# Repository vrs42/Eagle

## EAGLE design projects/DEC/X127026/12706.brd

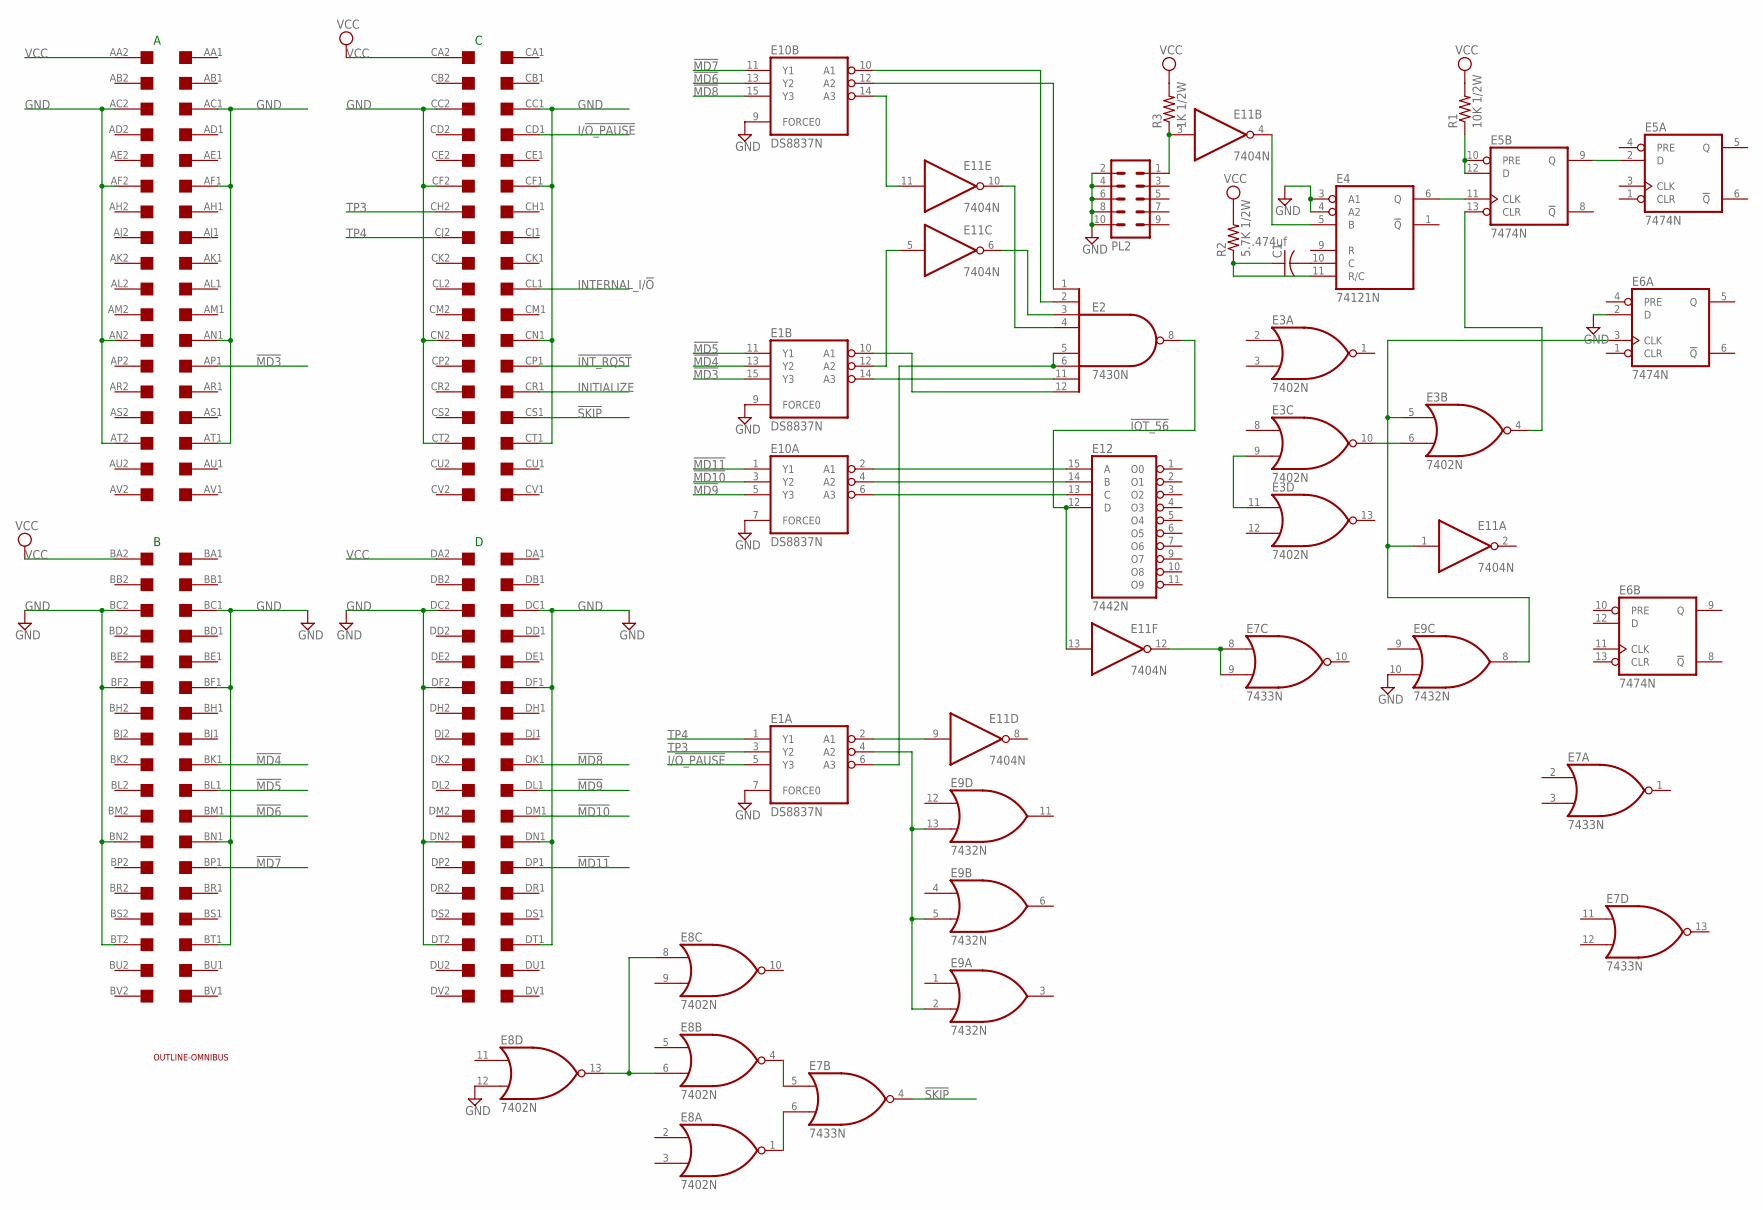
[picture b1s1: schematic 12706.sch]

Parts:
C1: .474uf; C050-045X075
E1, E10: DS8837N; DIL16
E2: 7430N; DIL14
E3, E8: 7402N; DIL14
E4: 74121N; DIL14
E5, E6: 7474N; DIL14
E7: 7433N; DIL14
E9: 7432N; DIL14
E11: 7404N; DIL14
E12: 7442N; DIL16
PL2: 10H
R1: 10K 1/2W; 0204/7
R2: 5.7K 1/2W; 0204/7
R3: 1K 1/2W; 0204/7
U$1: QUAD; EDGE-CON8
U$2: OUTLINE-OMNIBUS; OMNIBUS

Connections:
!INT_RQST: U$1.CP1
!IOT_56: E2.8 (O), E11.13 (I), E12.12 (D)
!MD3: E1.15 (Y3), U$1.AP1
!MD4: E1.13 (Y2), U$1.BK1
!MD5: E1.11 (Y1), U$1.BL1
!MD6: E10.13 (Y2), U$1.BM1
!MD7: E10.11 (Y1), U$1.BP1
!MD8: E10.15 (Y3), U$1.DK1
!MD9: E10.5 (Y3), U$1.DL1
!MD10: E10.3 (Y2), U$1.DM1
!MD11: E10.1 (Y1), U$1.DP1
!SKIP: E7.4 (O), U$1.CS1
GND: E1.7 (FORCE0), E1.8 (GND), E1.9 (FORCE0), E2.7 (GND), E3.7 (GND), E4.3 (A1), E4.4 (A2), E4.7 (GND), E5.7 (GND), E6.2 (D), E6.7 (GND), E7.7 (GND), E8.7 (GND), E8.12 (I1), E9.7 (GND), E9.10 (I1), E10.7 (FORCE0), E10.8 (GND), E10.9 (FORCE0), E11.7 (GND), E12.8 (GND), PL2.2, PL2.4, PL2.6, PL2.8, PL2.10, U$1.AC1, U$1.AC2, U$1.AF1, U$1.AF2, U$1.AN1, U$1.AN2, U$1.AT1, U$1.AT2, U$1.BC1, U$1.BC2, U$1.BF1, U$1.BF2, U$1.BN1, U$1.BN2, U$1.BT1, U$1.BT2, U$1.CC1, U$1.CC2, U$1.CF1, U$1.CF2, U$1.CN1, U$1.CN2, U$1.CT1, U$1.CT2, U$1.DC1, U$1.DC2, U$1.DF1, U$1.DF2, U$1.DN1, U$1.DN2, U$1.DT1, U$1.DT2
I/!O_PAUSE: E1.5 (Y3), U$1.CD1
INITIALIZE: U$1.CR1
INTERNAL_I/!O: U$1.CL1
unnamed: E1.14 (A3), E2.11 (I6)
unnamed: E1.10 (A1), E2.12 (I7)
unnamed: E10.2 (A1), E12.15 (A)
unnamed: E10.4 (A2), E12.14 (B)
unnamed: E10.6 (A3), E12.13 (C)
unnamed: E7.6 (I1), E8.1 (O)
unnamed: E7.8 (I0), E7.9 (I1), E11.12 (O)
unnamed: E1.2 (A1), E11.9 (I)
unnamed: E1.4 (A2), E9.2 (I1), E9.5 (I1), E9.13 (I1)
unnamed: E1.6 (A3), E2.5 (I4), E2.6 (I5)
unnamed: E2.4 (I3), E11.10 (O)
unnamed: E2.1 (I0), E10.12 (A2)
unnamed: E2.2 (I1), E10.10 (A1)
unnamed: E2.3 (I2), E11.6 (O)
unnamed: E1.12 (A2), E11.5 (I)
unnamed: E10.14 (A3), E11.11 (I)
unnamed: E7.5 (I0), E8.4 (O)
unnamed: E8.6 (I1), E8.8 (I0), E8.13 (O)
unnamed: C1.1, E4.11 (R/C), R2.1
unnamed: E5.2 (D), E5.9 (Q)
unnamed: E5.10 (PRE), E5.12 (D), R1.1
unnamed: E3.6 (I1), E3.10 (O)
unnamed: E3.9 (I1), E3.11 (I0)
unnamed: C1.2, E4.10 (C)
unnamed: E4.6 (Q), E5.11 (CLK)
unnamed: E4.5 (B), E11.4 (O)
unnamed: E11.3 (I), PL2.1, R3.1
unnamed: E3.4 (O), E5.13 (CLR)
unnamed: E3.5 (I0), E6.3 (CLK), E9.8 (O), E11.1 (I)
TP3: E1.3 (Y2), U$1.CH2
TP4: E1.1 (Y1), U$1.CJ2
VCC: E1.16 (VCC), E2.14 (VCC), E3.14 (VCC), E4.14 (VCC), E5.14 (VCC), E6.14 (VCC), E7.14 (VCC), E8.14 (VCC), E9.14 (VCC), E10.16 (VCC), E11.14 (VCC), E12.16 (VCC), R1.2, R2.2, R3.2, U$1.AA2, U$1.BA2, U$1.CA2, U$1.DA2

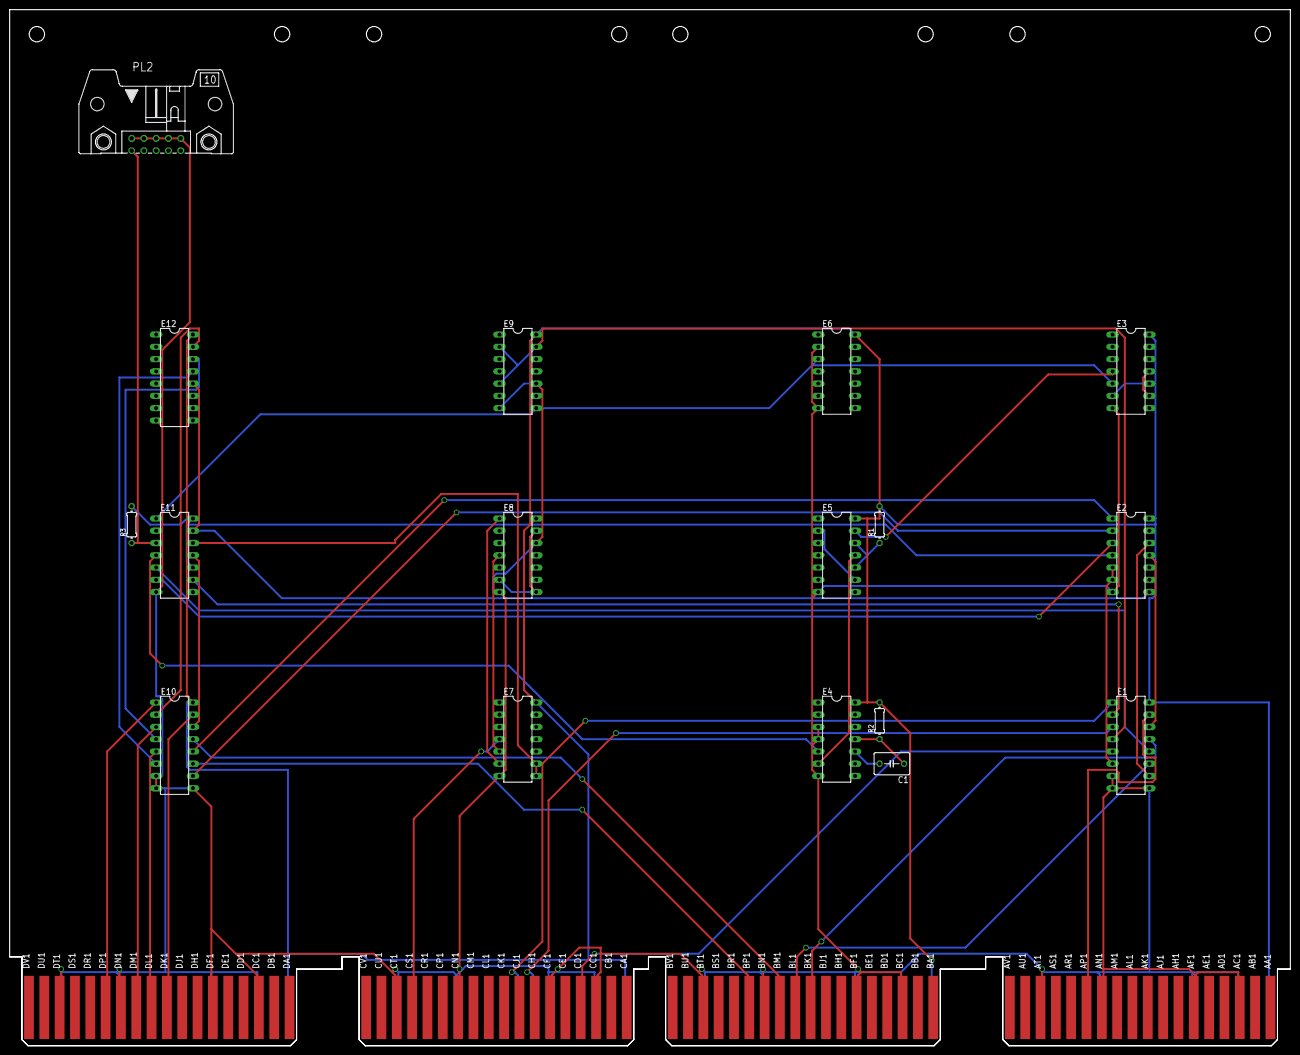
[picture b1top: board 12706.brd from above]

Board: 2 copper layers, 265.3 x 214.6 mm, 19 parts (0 on the bottom side), 45 nets.

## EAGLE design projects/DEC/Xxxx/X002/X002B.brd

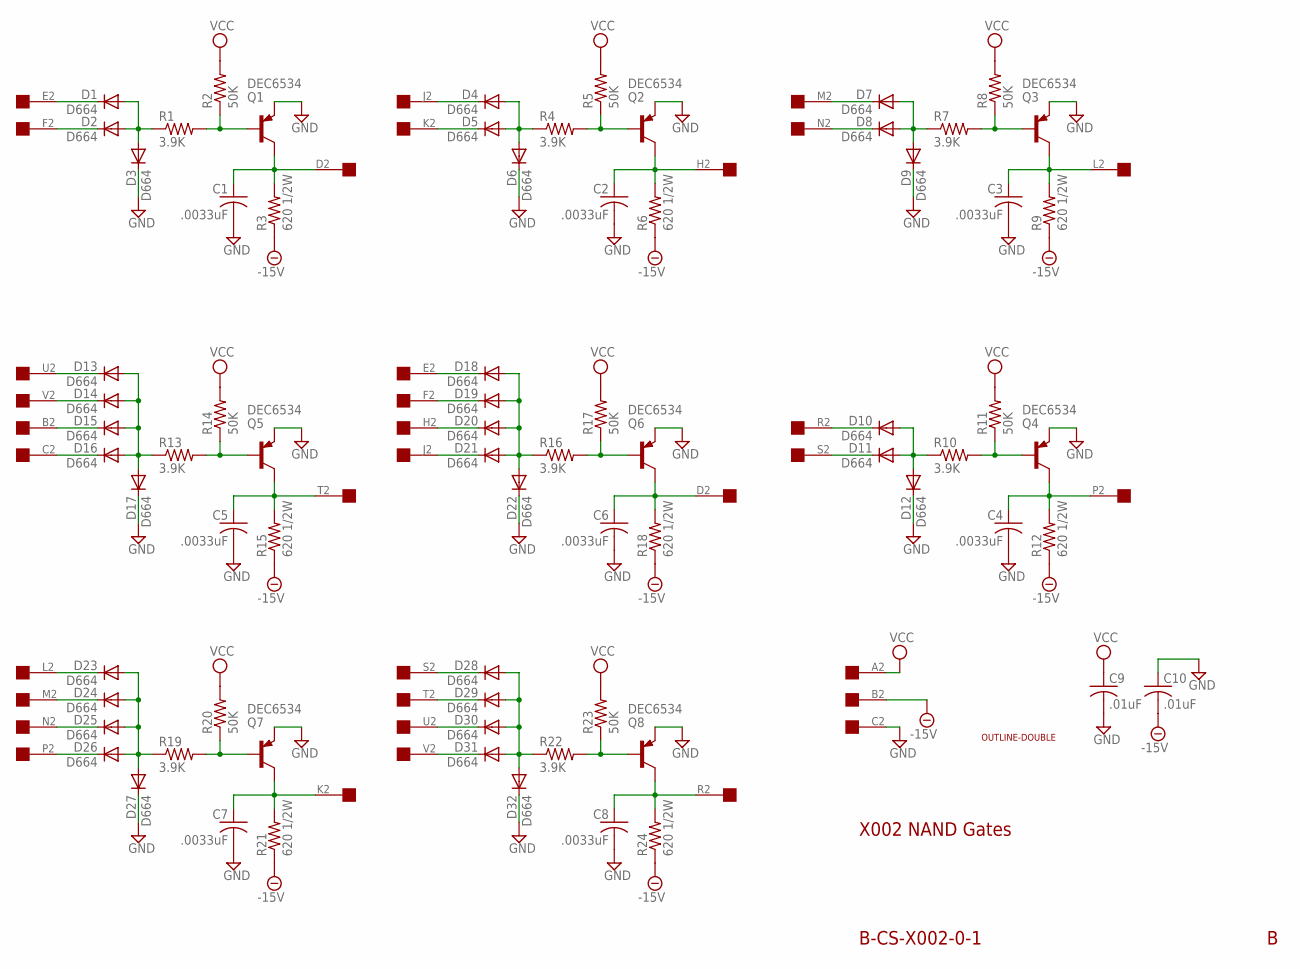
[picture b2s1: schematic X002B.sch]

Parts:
A: EDGE-1; EDGE-CON1
B: EDGE-1; EDGE-CON1
C1, C2, C3, C4, C5, C6, C7, C8: .0033uF; C225-062X268
C9, C10: .01uF; C050-025X075
D1, D2, D3, D4, D5, D6, D7, D8, D9, D10, D11, D12, D13, D14, D15, D16, D17, D18, D19, D20, D21, D22, D23, D24, D25, D26, D27, D28, D29, D30, D31, D32: D664; DO35-10
Q1, Q2, Q3, Q4, Q5, Q6, Q7, Q8: DEC6534; TO5
R1, R4, R7, R10, R13, R16, R19, R22: 3.9K; 0207/10
R2, R5, R8, R11, R14, R17, R20, R23: 50K; 0207/10
R3, R6, R9, R12, R15, R18, R21, R24: 620 1/2W; 0414/15
U$1: OUTLINE-DOUBLE; DOUBLE

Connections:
-15V: A.B2, C10.2, R3.1, R6.1, R9.1, R12.1, R15.1, R18.1, R21.1, R24.1
GND: A.C2, C1.2, C2.2, C3.2, C4.2, C5.2, C6.2, C7.2, C8.2, C9.2, C10.1, D3.C, D6.C, D9.C, D12.C, D17.C, D22.C, D27.C, D32.C, Q1.1 (E), Q2.1 (E), Q3.1 (E), Q4.1 (E), Q5.1 (E), Q6.1 (E), Q7.1 (E), Q8.1 (E)
unnamed: A.F2, D2.C
unnamed: A.E2, D1.C
unnamed: D1.A, D2.A, D3.A, R1.1
unnamed: Q1.2 (B), R1.2, R2.1
unnamed: A.D2, C1.1, Q1.3 (C), R3.2
unnamed: A.K2, D5.C
unnamed: A.J2, D4.C
unnamed: D4.A, D5.A, D6.A, R4.1
unnamed: Q2.2 (B), R4.2, R5.1
unnamed: A.H2, C2.1, Q2.3 (C), R6.2
unnamed: A.N2, D8.C
unnamed: A.M2, D7.C
unnamed: D7.A, D8.A, D9.A, R7.1
unnamed: Q3.2 (B), R7.2, R8.1
unnamed: A.L2, C3.1, Q3.3 (C), R9.2
unnamed: A.S2, D11.C
unnamed: A.R2, D10.C
unnamed: D10.A, D11.A, D12.A, R10.1
unnamed: Q4.2 (B), R10.2, R11.1
unnamed: A.P2, C4.1, Q4.3 (C), R12.2
unnamed: A.V2, D14.C
unnamed: A.U2, D13.C
unnamed: D13.A, D14.A, D15.A, D16.A, D17.A, R13.1
unnamed: Q5.2 (B), R13.2, R14.1
unnamed: A.T2, C5.1, Q5.3 (C), R15.2
unnamed: B.C2, D16.C
unnamed: B.B2, D15.C
unnamed: B.F2, D19.C
unnamed: B.E2, D18.C
unnamed: D18.A, D19.A, D20.A, D21.A, D22.A, R16.1
unnamed: Q6.2 (B), R16.2, R17.1
unnamed: B.D2, C6.1, Q6.3 (C), R18.2
unnamed: B.J2, D21.C
unnamed: B.H2, D20.C
unnamed: B.M2, D24.C
unnamed: B.L2, D23.C
unnamed: D23.A, D24.A, D25.A, D26.A, D27.A, R19.1
unnamed: Q7.2 (B), R19.2, R20.1
unnamed: B.K2, C7.1, Q7.3 (C), R21.2
unnamed: B.P2, D26.C
unnamed: B.N2, D25.C
unnamed: B.T2, D29.C
unnamed: B.S2, D28.C
unnamed: D28.A, D29.A, D30.A, D31.A, D32.A, R22.1
unnamed: Q8.2 (B), R22.2, R23.1
unnamed: B.R2, C8.1, Q8.3 (C), R24.2
unnamed: B.V2, D31.C
unnamed: B.U2, D30.C
VCC: A.A2, C9.1, R2.2, R5.2, R8.2, R11.2, R14.2, R17.2, R20.2, R23.2

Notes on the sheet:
B-CS-X002-0-1
X002 NAND Gates

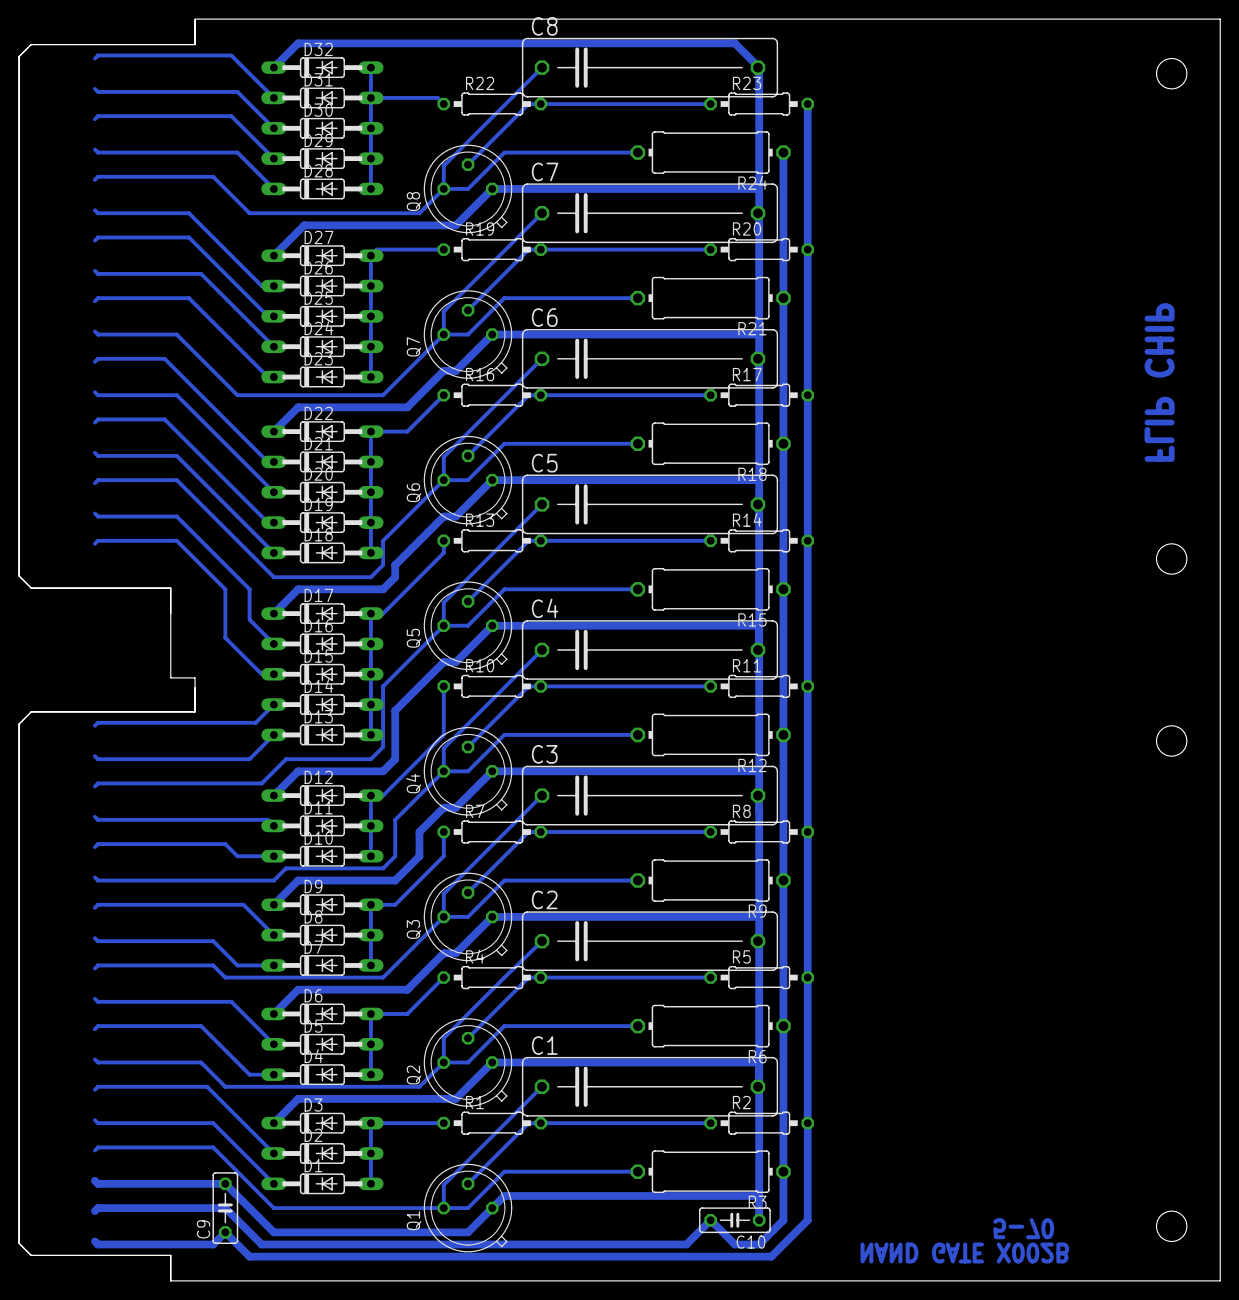
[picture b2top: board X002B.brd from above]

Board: 2 copper layers, 125.7 x 132.1 mm, 78 parts (1 on the bottom side), 51 nets.

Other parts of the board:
U$2: FLIPCHIP

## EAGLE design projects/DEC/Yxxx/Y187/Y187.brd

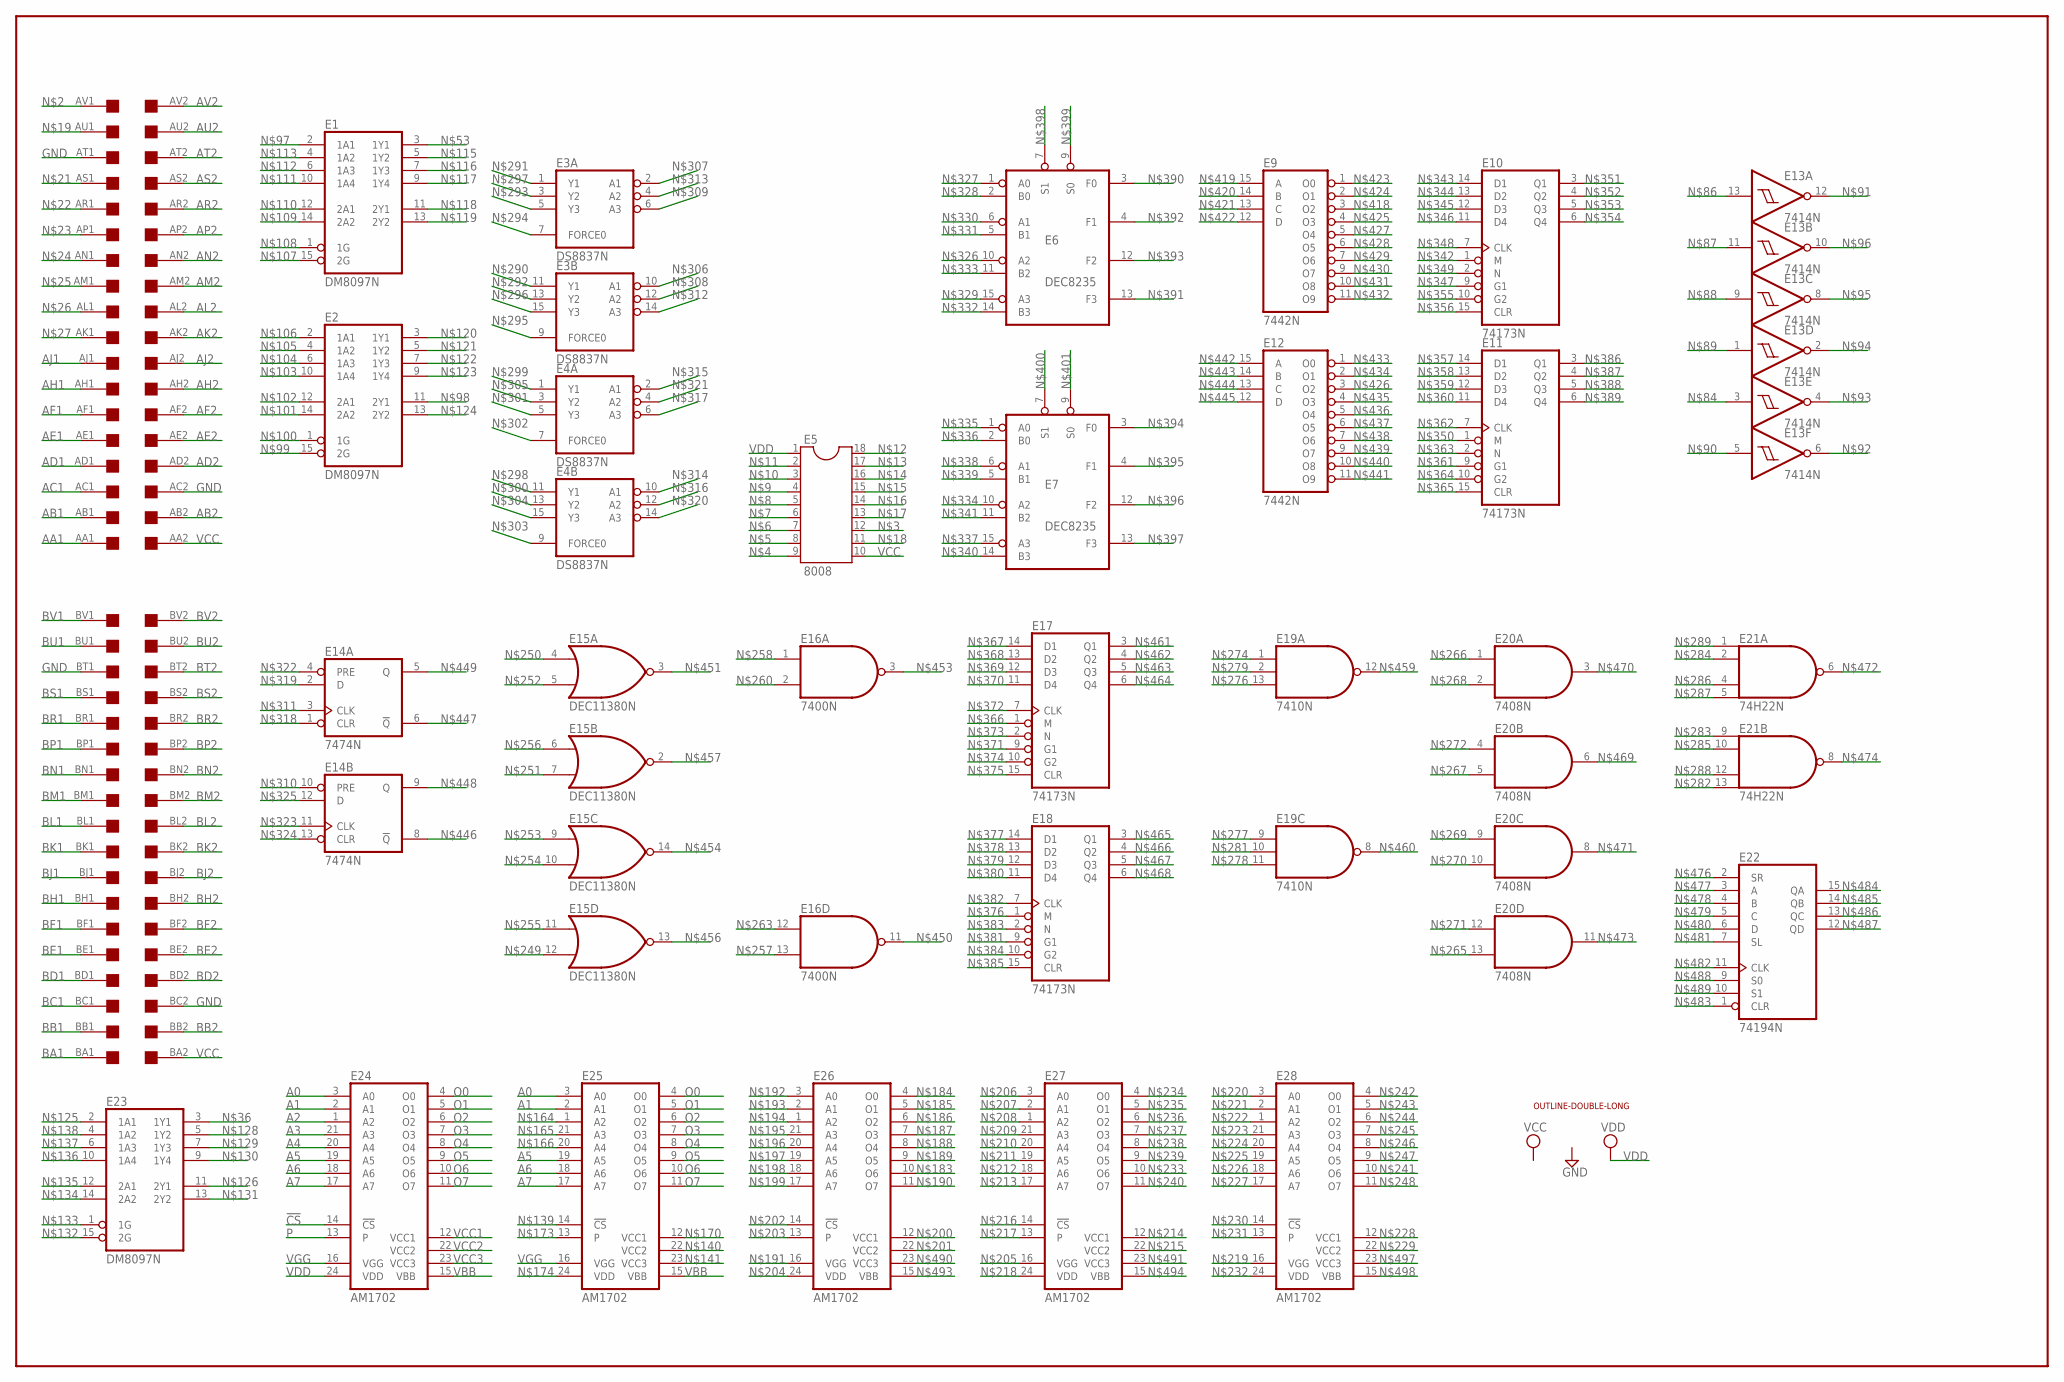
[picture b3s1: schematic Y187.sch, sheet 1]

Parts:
E1, E2, E23: DM8097N; DIL16
E3, E4: DS8837N; DIL16
E5: 8008; DIL18
E6, E7: DEC8235; DIL16
E9, E12: 7442N; DIL16
E10, E11, E17, E18: 74173N; DIL16
E13: 7414N; DIL14
E14: 7474N; DIL14
E15: DEC11380N; DIL14
E16: 7400N; DIL14
E19: 7410N; DIL14
E20: 7408N; DIL14
E21: 74H22N; DIL14
E22: 74194N; DIL16
E24, E25, E26, E27, E28: AM1702; DIL24
U$1: OUTLINE-DOUBLE-LONG; DOUBLE-LONG
U$2: DOUBLE; EDGE-CON4

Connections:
!CS: E24.14 (!CS)
A0: E24.3 (A0), E25.3 (A0)
A1: E24.2 (A1), E25.2 (A1)
A2: E24.1 (A2)
A3: E24.21 (A3)
A4: E24.20 (A4)
A5: E24.19 (A5), E25.19 (A5)
A6: E24.18 (A6), E25.18 (A6)
A7: E24.17 (A7), E25.17 (A7)
AA1: U$2.AA1
AB1: U$2.AB1
AB2: U$2.AB2
AC1: U$2.AC1
AD1: U$2.AD1
AD2: U$2.AD2
AE1: U$2.AE1
AE2: U$2.AE2
AF1: U$2.AF1
AF2: U$2.AF2
AH1: U$2.AH1
AH2: U$2.AH2
AJ1: U$2.AJ1
AJ2: U$2.AJ2
AK2: U$2.AK2
AL2: U$2.AL2
AM2: U$2.AM2
AN2: U$2.AN2
AP2: U$2.AP2
AR2: U$2.AR2
AS2: U$2.AS2
AT2: U$2.AT2
AU2: U$2.AU2
AV2: U$2.AV2
BA1: U$2.BA1
BB1: U$2.BB1
BB2: U$2.BB2
BC1: U$2.BC1
BD1: U$2.BD1
BD2: U$2.BD2
BE1: U$2.BE1
BE2: U$2.BE2
BF1: U$2.BF1
BF2: U$2.BF2
BH1: U$2.BH1
BH2: U$2.BH2
BJ1: U$2.BJ1
BJ2: U$2.BJ2
BK1: U$2.BK1
BK2: U$2.BK2
BL1: U$2.BL1
BL2: U$2.BL2
BM1: U$2.BM1
BM2: U$2.BM2
BN1: U$2.BN1
BN2: U$2.BN2
BP1: U$2.BP1
BP2: U$2.BP2
BR1: U$2.BR1
BR2: U$2.BR2
BS1: U$2.BS1; also elsewhere on the board
BS2: U$2.BS2
BT2: U$2.BT2
BU1: U$2.BU1; also elsewhere on the board
BU2: U$2.BU2
BV1: U$2.BV1; also elsewhere on the board
BV2: U$2.BV2
GND: E1.8 (GND), E2.8 (GND), E3.8 (GND), E4.8 (GND), E6.8 (GND), E7.8 (GND), E9.8 (GND), E10.8 (GND), E11.8 (GND), E12.8 (GND), E13.7 (GND), E14.7 (GND), E15.1 (GND), E16.7 (GND), E17.8 (GND), E18.8 (GND), E19.7 (GND), E20.7 (GND), E21.7 (GND), E22.8 (GND), E23.8 (GND), U$2.AC2, U$2.AT1, U$2.BC2, U$2.BT1; also elsewhere on the board
O0: E24.4 (O0), E25.4 (O0)
O1: E24.5 (O1), E25.5 (O1)
O2: E24.6 (O2), E25.6 (O2)
O3: E24.7 (O3), E25.7 (O3)
O4: E24.8 (O4), E25.8 (O4)
O5: E24.9 (O5), E25.9 (O5)
O6: E24.10 (O6), E25.10 (O6)
O7: E24.11 (O7), E25.11 (O7)
P: E24.13
VBB: E24.15 (VBB), E25.15 (VBB)
VCC: E1.16 (VCC), E2.16 (VCC), E3.16 (VCC), E4.16 (VCC), E5.10, E6.16 (VCC), E7.16 (VCC), E9.16 (VCC), E10.16 (VCC), E11.16 (VCC), E12.16 (VCC), E13.14 (VCC), E14.14 (VCC), E15.8 (VCC), E16.14 (VCC), E17.16 (VCC), E18.16 (VCC), E19.14 (VCC), E20.14 (VCC), E21.14 (VCC), E22.16 (VCC), E23.16 (VCC), U$2.AA2, U$2.BA2; also elsewhere on the board
VCC1: E24.12 (VCC1)
VCC2: E24.22 (VCC2)
VCC3: E24.23 (VCC3)
VDD: E5.1, E24.24 (VDD)
VGG: E24.16 (VGG), E25.16 (VGG)

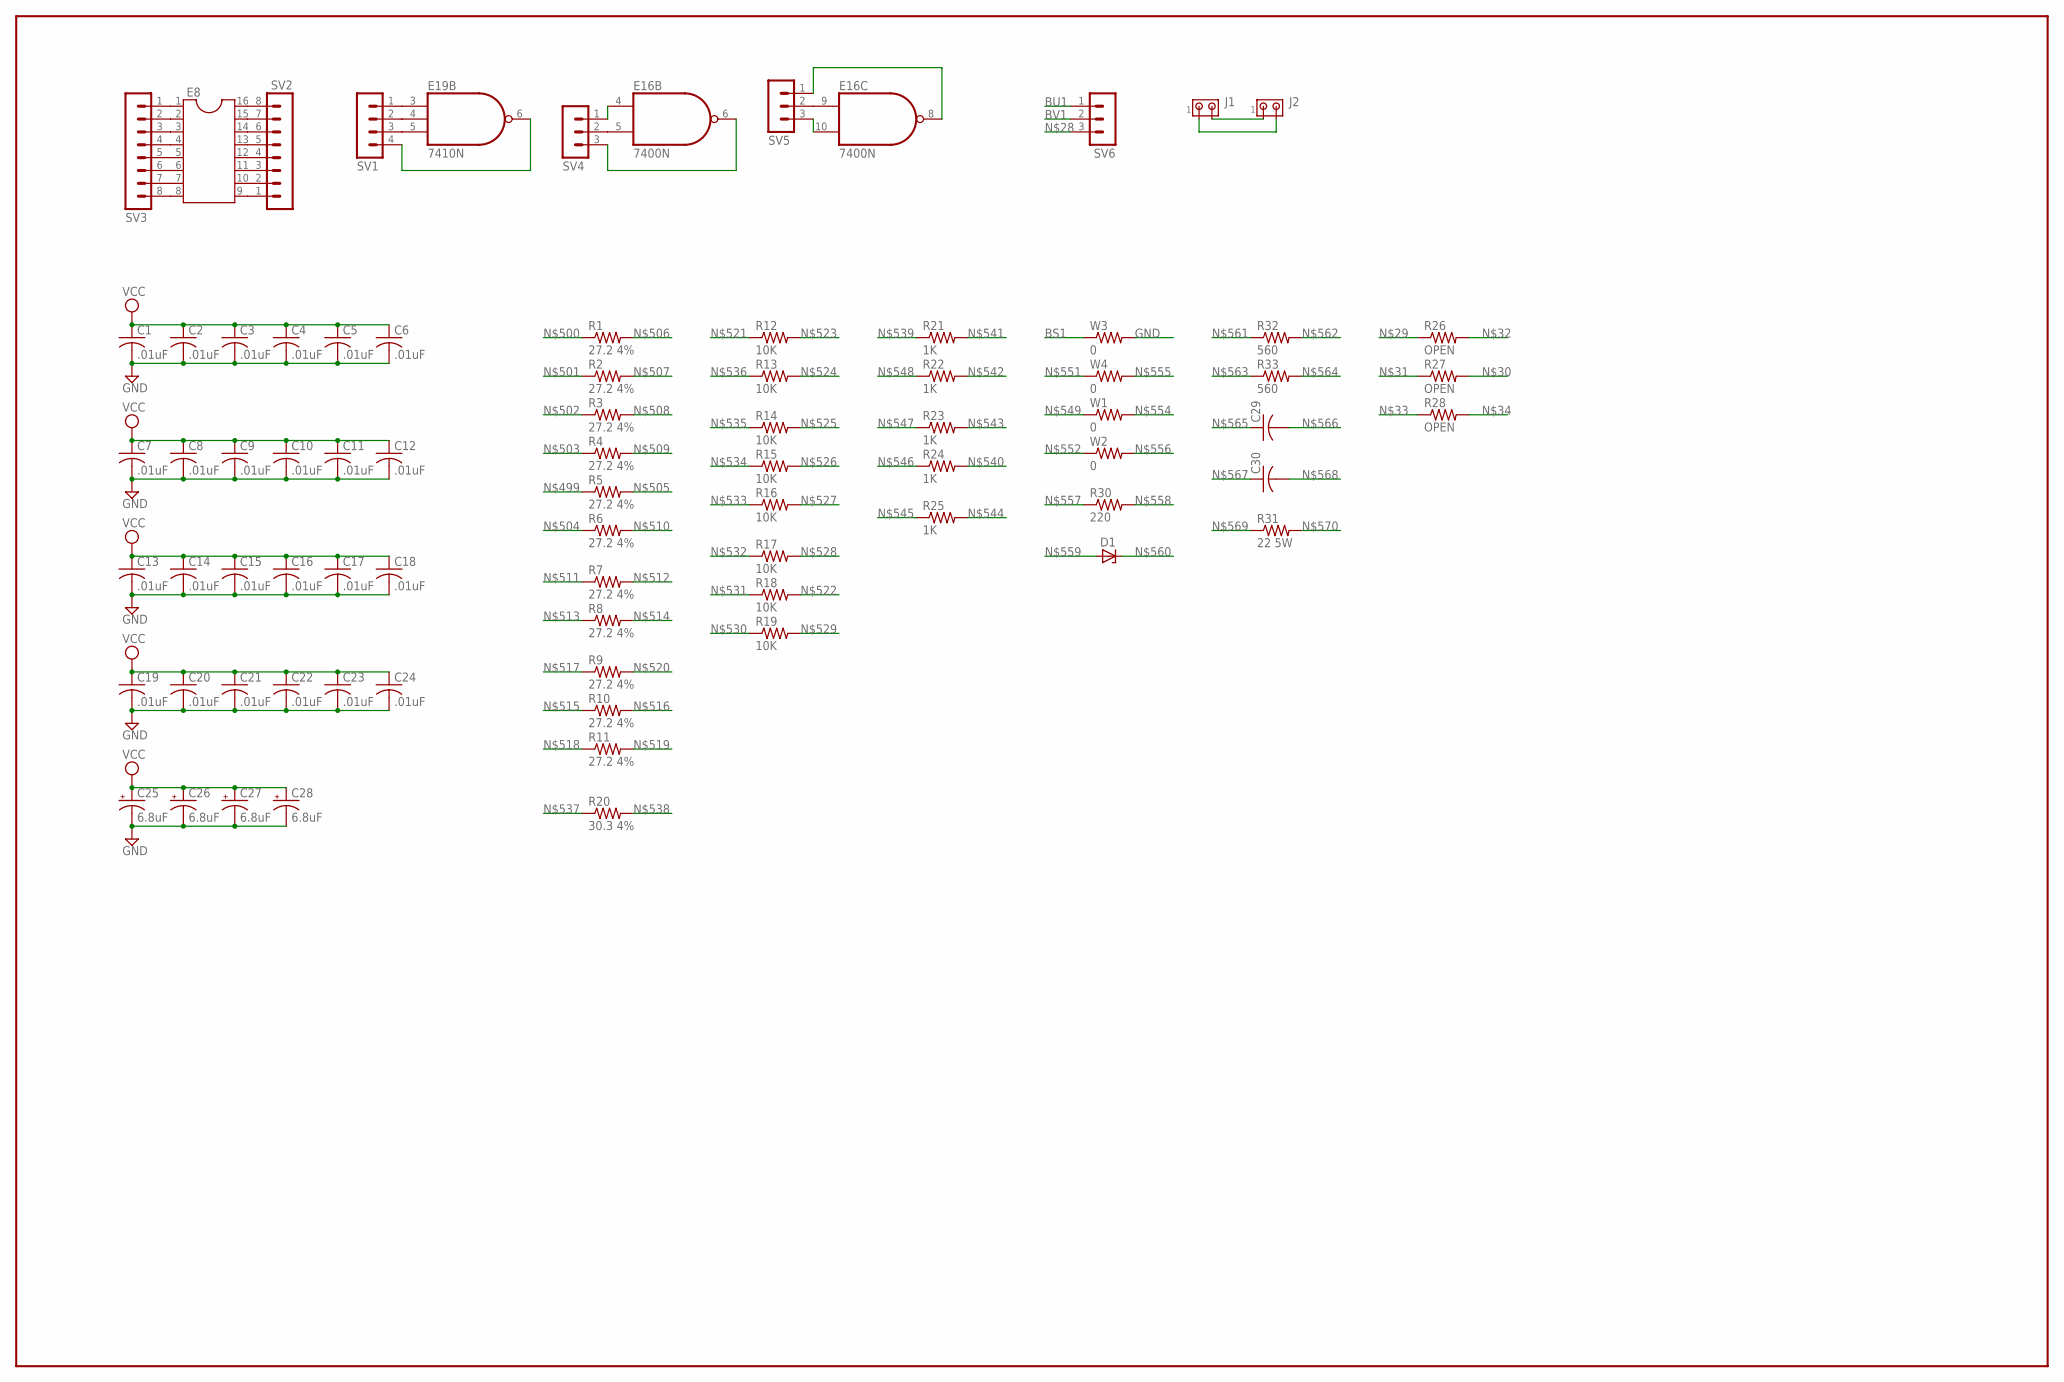
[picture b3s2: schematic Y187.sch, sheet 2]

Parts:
C1, C2, C3, C4, C5, C6, C7, C8, C9, C10, C11, C12, C13, C14, C15, C16, C17, C18, C19, C20, C21, C22, C23, C24: .01uF; C075-032X103
C25, C26, C27, C28: 6.8uF; E12-8
C29, C30: C-US075-032X103; C075-032X103
D1: ZENER-DIODEDO35Z10; DO35Z10
E8: DIL16
E16: 7400N; DIL14
E19: 7410N; DIL14
J1, J2: MTA02-100; 10X02MTA
R1, R2, R3, R4, R5, R6, R7, R8, R9, R10, R11: 27.2 4%; 0207/10
R12, R13, R14, R15, R16, R17, R18, R19: 10K; 0207/10
R20: 30.3 4%; 0207/10
R21, R22, R23, R24, R25: 1K; 0207/10
R26, R27, R28: OPEN; 0207/10
R30: 220; 0207/10
R31: 22 5W; 0617/22
R32, R33: 560; 0207/10
SV1: MA04-1
SV2, SV3: MA08-1
SV4, SV5, SV6: MA03-1
W1, W2, W3, W4: 0; 0207/10

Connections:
BS1: W3.1; also elsewhere on the board
BU1: SV6.1; also elsewhere on the board
BV1: SV6.2; also elsewhere on the board
GND: C1.2, C2.2, C3.2, C4.2, C5.2, C6.2, C7.2, C8.2, C9.2, C10.2, C11.2, C12.2, C13.2, C14.2, C15.2, C16.2, C17.2, C18.2, C19.2, C20.2, C21.2, C22.2, C23.2, C24.2, C25.-, C26.-, C27.-, C28.-, E16.7 (GND), E19.7 (GND), W3.2; also elsewhere on the board
unnamed: J1.2, J2.1
unnamed: J1.1, J2.2
unnamed: E16.5 (I1), SV4.2
unnamed: E16.4 (I0), SV4.1
unnamed: E16.9 (I0), SV5.2
unnamed: E16.10 (I1), SV5.3
unnamed: E19.3 (I0), SV1.1
unnamed: E19.4 (I1), SV1.2
unnamed: E19.5 (I2), SV1.3
unnamed: E8.1, SV3.1
unnamed: E8.2, SV3.2
unnamed: E8.3, SV3.3
unnamed: E8.4, SV3.4
unnamed: E8.5, SV3.5
unnamed: E8.6, SV3.6
unnamed: E8.7, SV3.7
unnamed: E8.8, SV3.8
unnamed: E8.9, SV2.1
unnamed: E8.10, SV2.2
unnamed: E8.11, SV2.3
unnamed: E8.12, SV2.4
unnamed: E8.13, SV2.5
unnamed: E8.14, SV2.6
unnamed: E8.15, SV2.7
unnamed: E8.16, SV2.8
unnamed: E16.6 (O), SV4.3
unnamed: E16.8 (O), SV5.1
unnamed: E19.6 (O), SV1.4
VCC: C1.1, C2.1, C3.1, C4.1, C5.1, C6.1, C7.1, C8.1, C9.1, C10.1, C11.1, C12.1, C13.1, C14.1, C15.1, C16.1, C17.1, C18.1, C19.1, C20.1, C21.1, C22.1, C23.1, C24.1, C25.+, C26.+, C27.+, C28.+, E16.14 (VCC), E19.14 (VCC); also elsewhere on the board

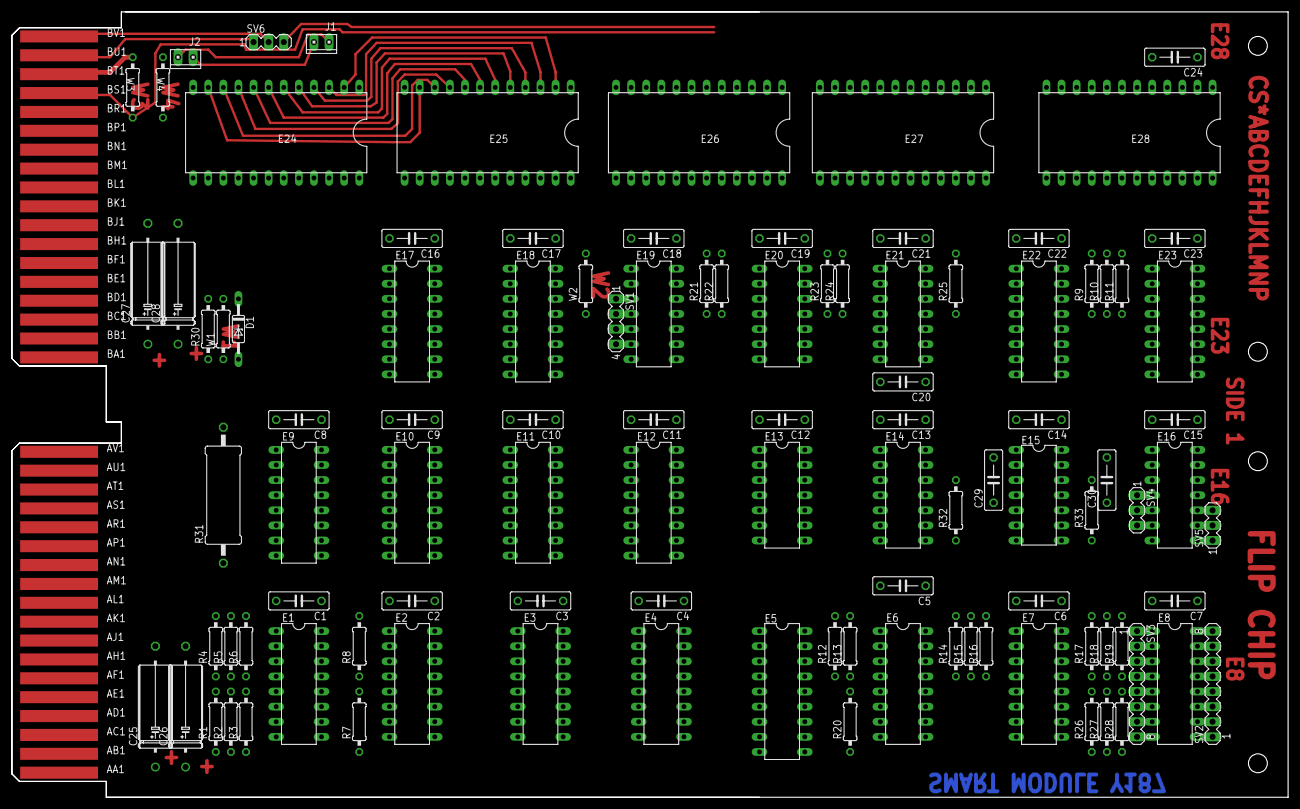
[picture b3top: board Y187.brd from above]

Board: 2 copper layers, 214.6 x 132.1 mm, 105 parts (0 on the bottom side), 49 nets.

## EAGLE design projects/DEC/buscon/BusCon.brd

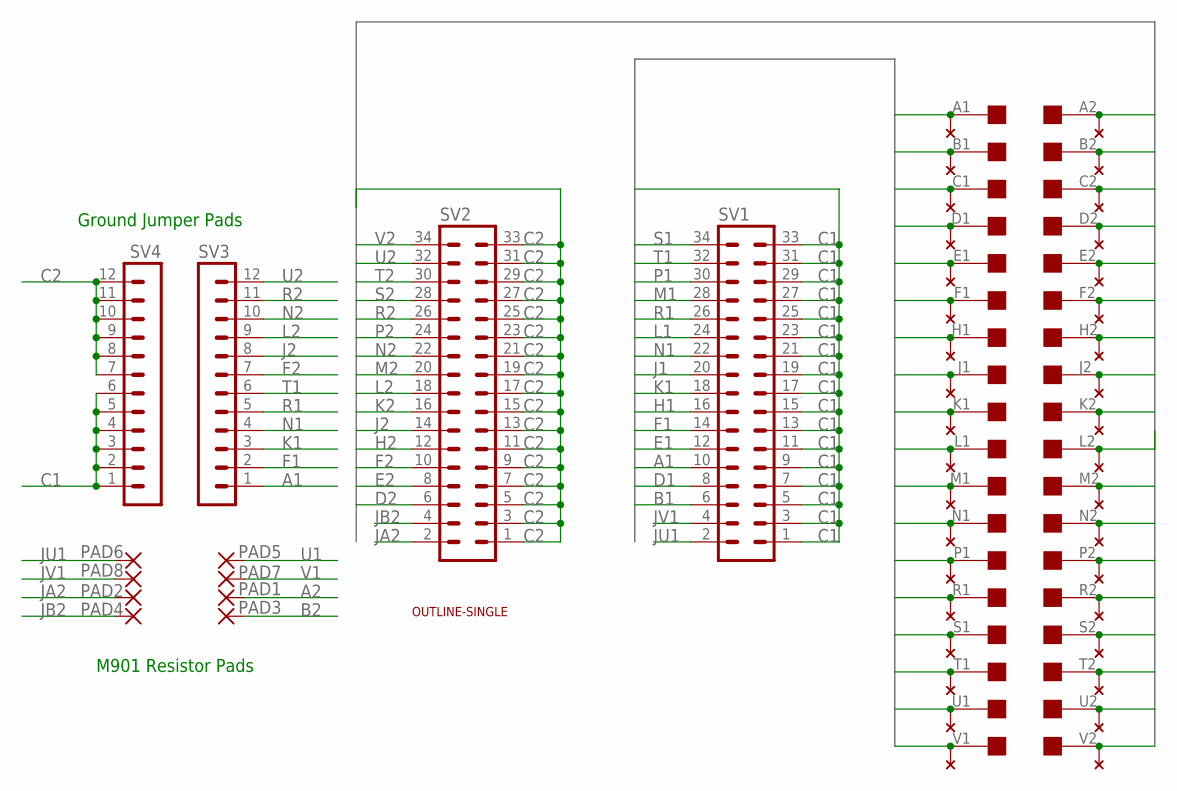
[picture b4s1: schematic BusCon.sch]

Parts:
PAD1, PAD2, PAD3, PAD4, PAD5, PAD6, PAD7, PAD8: 1,6/0,8
SV1, SV2: MA17-2
SV3, SV4: MA12-1
U$1: OUTLINE-SINGLE; SINGLE
U$4: SINGLE; EDGE-CON2
U$5: THRU-HOLE2C; THRU-HOLEC

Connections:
A1: SV1.10, SV3.1, U$4.A1, U$5.A1
A2: PAD1.1, U$4.A2, U$5.A2
B1: SV1.6, U$4.B1, U$5.B1
B2: PAD3.1, U$4.B2, U$5.B2
C1: SV1.1, SV1.3, SV1.5, SV1.7, SV1.9, SV1.11, SV1.13, SV1.15, SV1.17, SV1.19, SV1.21, SV1.23, SV1.25, SV1.27, SV1.29, SV1.31, SV1.33, SV4.1, SV4.2, SV4.3, SV4.4, SV4.5, SV4.6, U$4.C1, U$5.C1
C2: SV2.1, SV2.3, SV2.5, SV2.7, SV2.9, SV2.11, SV2.13, SV2.15, SV2.17, SV2.19, SV2.21, SV2.23, SV2.25, SV2.27, SV2.29, SV2.31, SV2.33, SV4.7, SV4.8, SV4.9, SV4.10, SV4.11, SV4.12, U$4.C2, U$5.C2
D1: SV1.8, U$4.D1, U$5.D1
D2: SV2.6, U$4.D2, U$5.D2
E1: SV1.12, U$4.E1, U$5.E1
E2: SV2.8, U$4.E2, U$5.E2
F1: SV1.14, SV3.2, U$4.F1, U$5.F1
F2: SV2.10, SV3.7, U$4.F2, U$5.F2
H1: SV1.16, U$4.H1, U$5.H1
H2: SV2.12, U$4.H2, U$5.H2
J1: SV1.20, U$4.J1, U$5.J1
J2: SV2.14, SV3.8, U$4.J2, U$5.J2
JA2: PAD2.1, SV2.2
JB2: PAD4.1, SV2.4
JU1: PAD6.1, SV1.2
JV1: PAD8.1, SV1.4
K1: SV1.18, SV3.3, U$4.K1, U$5.K1
K2: SV2.16, U$4.K2, U$5.K2
L1: SV1.24, U$4.L1, U$5.L1
L2: SV2.18, SV3.9, U$4.L2, U$5.L2
M1: SV1.28, U$4.M1, U$5.M1
M2: SV2.20, U$4.M2, U$5.M2
N1: SV1.22, SV3.4, U$4.N1, U$5.N1
N2: SV2.22, SV3.10, U$4.N2, U$5.N2
P1: SV1.30, U$4.P1, U$5.P1
P2: SV2.24, U$4.P2, U$5.P2
R1: SV1.26, SV3.5, U$4.R1, U$5.R1
R2: SV2.26, SV3.11, U$4.R2, U$5.R2
S1: SV1.34, U$4.S1, U$5.S1
S2: SV2.28, U$4.S2, U$5.S2
T1: SV1.32, SV3.6, U$4.T1, U$5.T1
T2: SV2.30, U$4.T2, U$5.T2
U1: PAD5.1, U$4.U1, U$5.U1
U2: SV2.32, SV3.12, U$4.U2, U$5.U2
V1: PAD7.1, U$4.V1, U$5.V1
V2: SV2.34, U$4.V2, U$5.V2

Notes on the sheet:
M901 Resistor Pads
Ground Jumper Pads

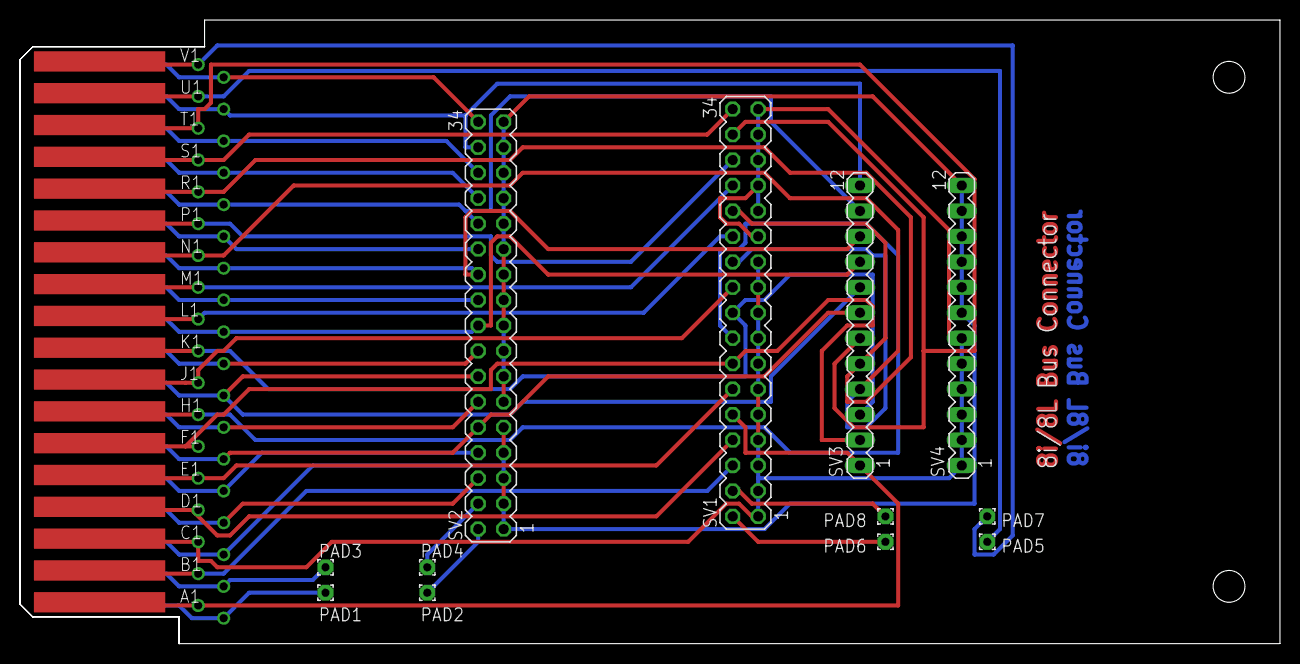
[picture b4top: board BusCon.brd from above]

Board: 2 copper layers, 125.7 x 62.2 mm, 15 parts (0 on the bottom side), 40 nets.

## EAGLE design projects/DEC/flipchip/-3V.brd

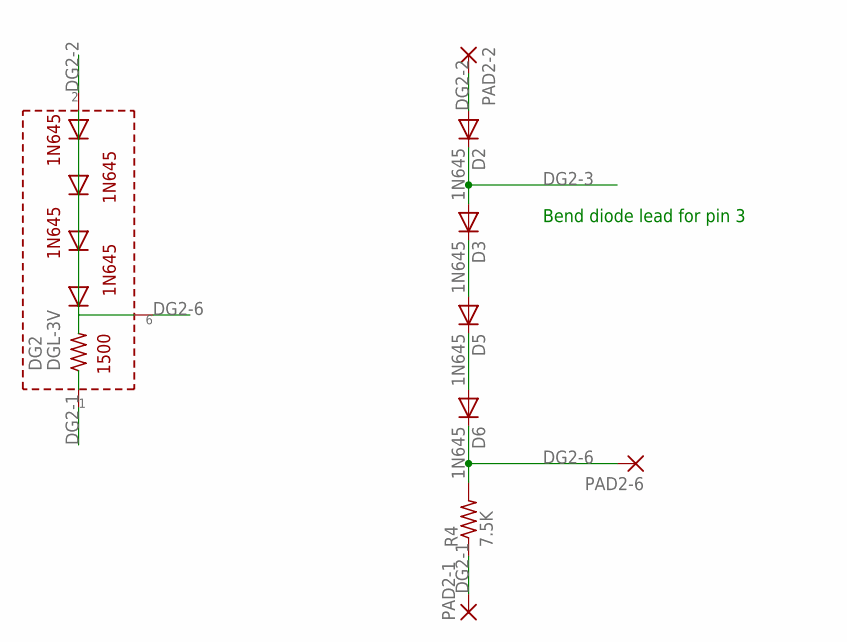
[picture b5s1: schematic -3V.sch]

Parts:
D2, D3, D5, D6: 1N645; DO34-7
DG2: DGL-3V; DGL2
PAD2-1, PAD2-2, PAD2-6: 1,6/0,8
R4: 7.5K; 0207/7

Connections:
DG2-1: DG2.P$1 (1), PAD2-1.1, R4.1
DG2-2: D2.A, DG2.P$2 (2), PAD2-2.1
DG2-3: D2.C, D3.A
DG2-6: D6.C, DG2.P$6 (6), PAD2-6.1, R4.2
unnamed: D5.C, D6.A
unnamed: D3.C, D5.A

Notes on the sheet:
Bend diode lead for pin 3

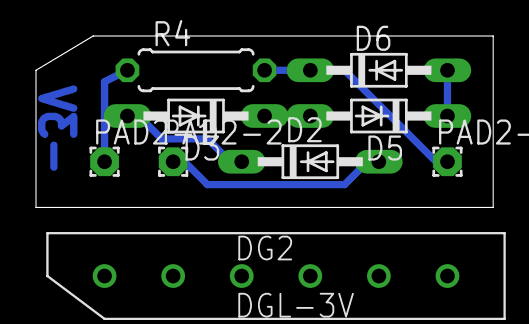
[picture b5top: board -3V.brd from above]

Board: 2 copper layers, 25.4 x 9.5 mm, 9 parts (0 on the bottom side), 6 nets.
